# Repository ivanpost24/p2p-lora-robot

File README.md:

# WIoT final project

Authored by: Farjan Ahmed, Carlos Giron, Ivan Post

This is our final project for CS 4501: Wireless for the Internet of Things. It is a prototype system for controlling a mobile robot over long distances (from our observation, up to 0.32 km) using the LoRa physical layer protocol on Heltec ESP32 v3 LORA boards. It is designed to operate on the 915 MHz unlicensed band in the United States, which means you do not need an amateur radio license to use it. [This is a video of an operator controlling the robot from about 0.3 km away](https://drive.google.com/file/d/1XLk9izT9hsWHlGPpsFzeZ8Zzyy3jfpdS/view?usp=sharing); the control latency is primarily due to delays in the video feed and is under 500 ms in practice. The exact feasible range will depend on environmental factors.

We have provided instructions below to reproduce our prototype.

## Building the peripheral robot

### Components list:
* [WiFi LoRa 32 V3](https://heltec.org/project/wifi-lora-32-v3/) Heltec Board
* 2 [Sparkfun Dual tb6612fng Motor Drivers](https://www.sparkfun.com/sparkfun-motor-driver-dual-tb6612fng-1a.html) for motor control
* 4 [12V DC 100RPM Greartisan](amazon.com/Greartisan-Electric-Reduction-Centric-Diameter/dp/B072R57C56/ref=sr_1_6?crid=129Y1UB2Q6AGI&dib=eyJ2IjoiMSJ9.DwmBOBIYZeCSiQA5saHHIxj7DpqChe3S76xeKR8zBhYkiYd1JqMtlKpyXpX8ml9P-PodyTQpF1U53Aiup88Gdk4xNOoXEbOCuZ-eF9qleWwFV8hyrN2Rm18CDetzJ0f9fudnr4t8DZx4H_xdhjciGS_N9iVl0n4egDoUJzDH8lzn89O2e6Xu7hb-V0s1TQMCYfGA-40lgYDVYd1WclO5MOMkNcvgmsqaYL5KdbTtvnZBJRt6uXWlYDs0ATjglZvQkKjh9Chfi3PU3360LFzHv60yV7CS9oWNygZAhhukyWI.Be_9xpxrY9lM7WvLv97bnTWI3TeSQBAD8dNGXVNmA04&dib_tag=se&keywords=greartisan&qid=1778122489&sprefix=greara%2Caps%2C104&sr=8-6) Motors
* [INIU Portable Power Bank](https://www.amazon.com/INIU-Portable-Slimmest-Powerbank-Compatible/dp/B0DC9PV394/ref=sr_1_4?crid=18OPPD3YMVHBW&dib=eyJ2IjoiMSJ9.0WQzVjTrLphPpYXHXLB68u4mBA5Rbn288wfA5sWyp35DpGtrewRhO8osgHukWIII1DwwZKSDCB8bNecpqMsOLGRi4OvMCrledarzWXZo2mm3vVUFbNUYvgteSJSiUC4W4GYlY3ICUgLDd70C-CZUId6LxWdVb2gp8cnrTH14hRnbeg_DZL2gJpJ-KxWzOnmqB7snAoO4SP9RmN1tobYXKDJH2LOSkcSvpj6yAEEGyvA.t-OCLLBvhl4AjC0RjoiDnJkgwEFwfezcISsImUpkACE&dib_tag=se&keywords=inui%2Bpower%2Bbank&qid=1778122614&sprefix=inui%2Bpower%2Bbank%2B%2Caps%2C218&sr=8-4&th=1)
* [ACEIRMC USB Power Delivery Module](https://www.amazon.com/ACEIRMC-Trigger-Polling-Detector-Notebook/dp/B0BTHXKM91/ref=sxin_17_pa_sp_search_thematic_sspa?content-id=amzn1.sym.354b3233-22c2-4681-93ae-c50603e79747%3Aamzn1.sym.354b3233-22c2-4681-93ae-c50603e79747&crid=441D3EZMIEG8&cv_ct_cx=pd+module&keywords=pd+module&pd_rd_i=B0BTHXKM91&pd_rd_r=e3bb3bd6-a17f-436b-9dd3-0978a650ec78&pd_rd_w=KqERS&pd_rd_wg=o0LLY&pf_rd_p=354b3233-22c2-4681-93ae-c50603e79747&pf_rd_r=KJ86FRZV0K8ABR1RP7X3&qid=1778122403&s=electronics&sbo=RZvfv%2F%2FHxDF%2BO5021pAnSA%3D%3D&sprefix=pd+modul%2Celectronics%2C102&sr=1-1-9630ce6b-eb04-480e-8729-567d2ef7dacb-spons&aref=fOHUb9EmTP&sp_csd=d2lkZ2V0TmFtZT1zcF9zZWFyY2hfdGhlbWF0aWM&psc=1) for requesting 12V from a power bank
* [HiLetgo game joystick](amazon.com/HiLetgo-Controller-JoyStick-Breakout-Arduino/dp/B00P7QBGD2)

Additional pcb relevant components such as resistors, switches, and connectors are shown in this schematic:

The KiCad files for editing the schematic and gerbers for ordering PCBs are included in the "/KiCad" directory.

Mount the breakout boards for motor drivers and modules onto their respective locations on the pcb:

## Building the central controller
### Pin assignments:
Assignments for the peripheral robot device are as follows:
* 19 - PWMA/B
* 20 - A/BIN1
* 26 - A/BIN2
* 47 - PWMA/B
* 48 - A/BIN1
* 33 - A/BIN2
* Connect external 3v3 supply and gnd

These pins are used to set the direction of motors and speed of motors as they are connected to tb6612fng motor drivers. You **MUST NOT** power the motor drivers using the 3v3 pins of the Heltec board. Due to a hardware issue it seems that these boards are unable to power the motor drivers and remain on for operation. You must use a seperate 3v3 source to power the drivers.

In our case we used an *Arduino Uno R3* to deliver 3v3, but a simple battery should suffice. It is important to remember to ground both Arduino and Heltec on the same rail otherwise reference issues for digital logic occur.

Assignments for the central controller are as follows:
* 7 - Vrx
* 6 - Vry
* 5 - Sw

Although the datasheet recommends using 5V as input, our code was designed around using 3v3.

## Deploying the provided code

This project uses PlatformIO, so configuring the project locally should be simple. Flash the Heltec v3 on the robot with the lora-peripheral code, and flash the Heltec v3 on the controller with the lora-central code. Everything should start automatically without any user input.

## Starting the robot
After code has been flashed onto the central and peripheral devices start the device as follows:
1. Connect the power delivery module to the power bank's 65 W output port
2. Connect the Arduino to the power bank
3. Connect the Heltec to the power bank
4. Flip the enable switch

If the PD module and onboard led are on then the robot is ready for operation if the devices were flashed successfully and connections were correct.

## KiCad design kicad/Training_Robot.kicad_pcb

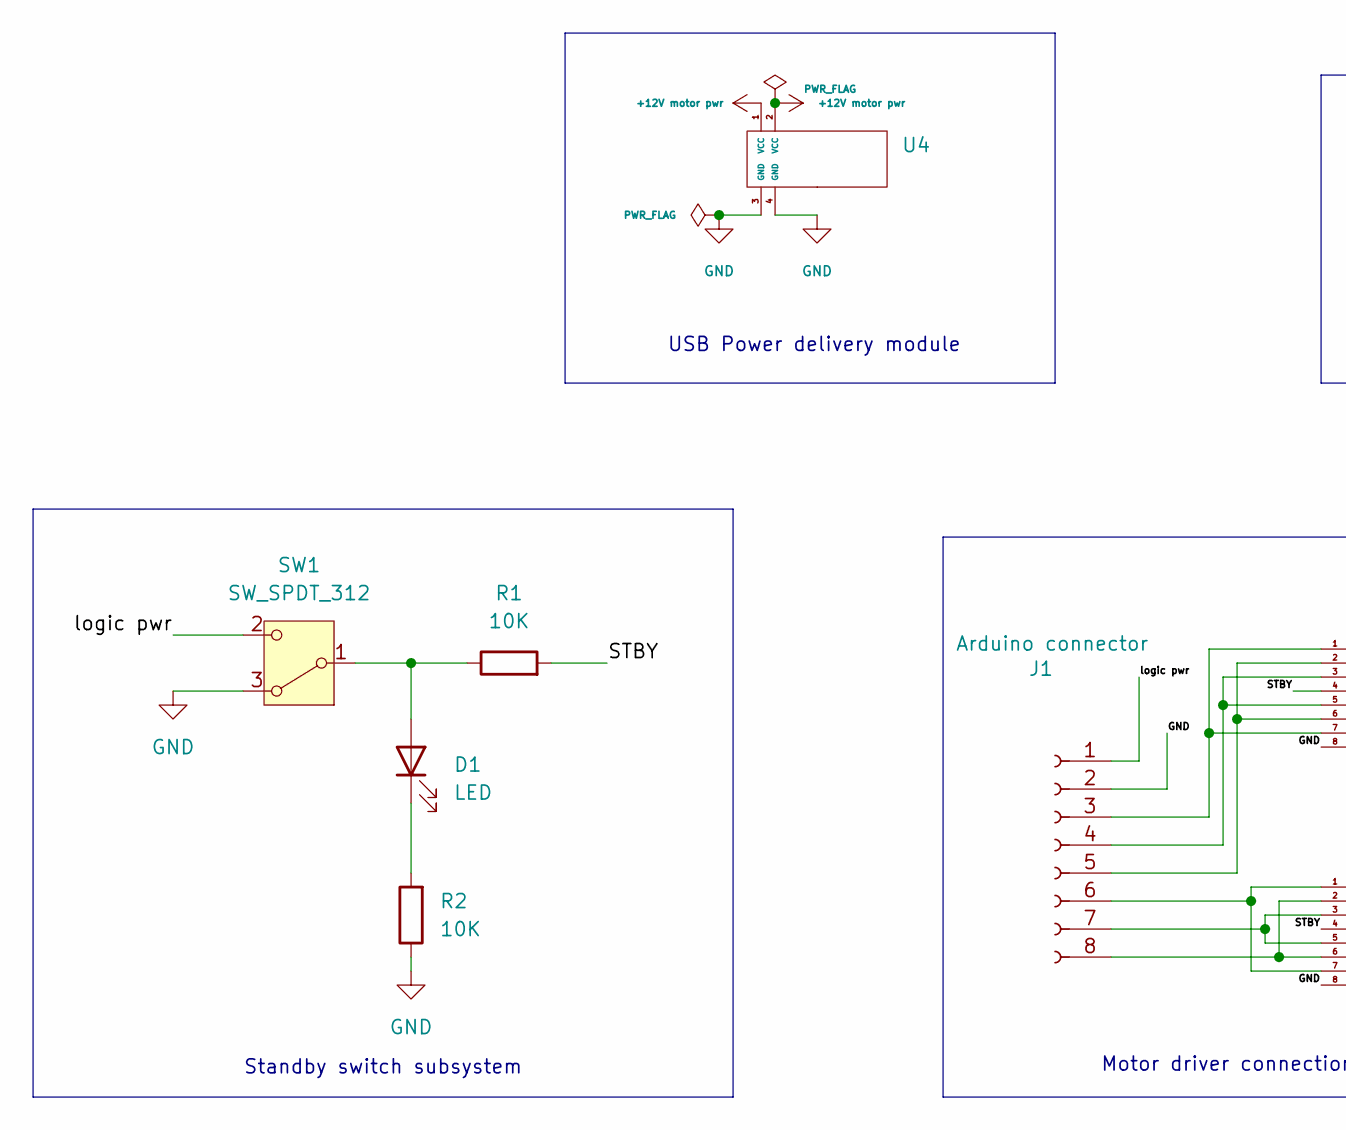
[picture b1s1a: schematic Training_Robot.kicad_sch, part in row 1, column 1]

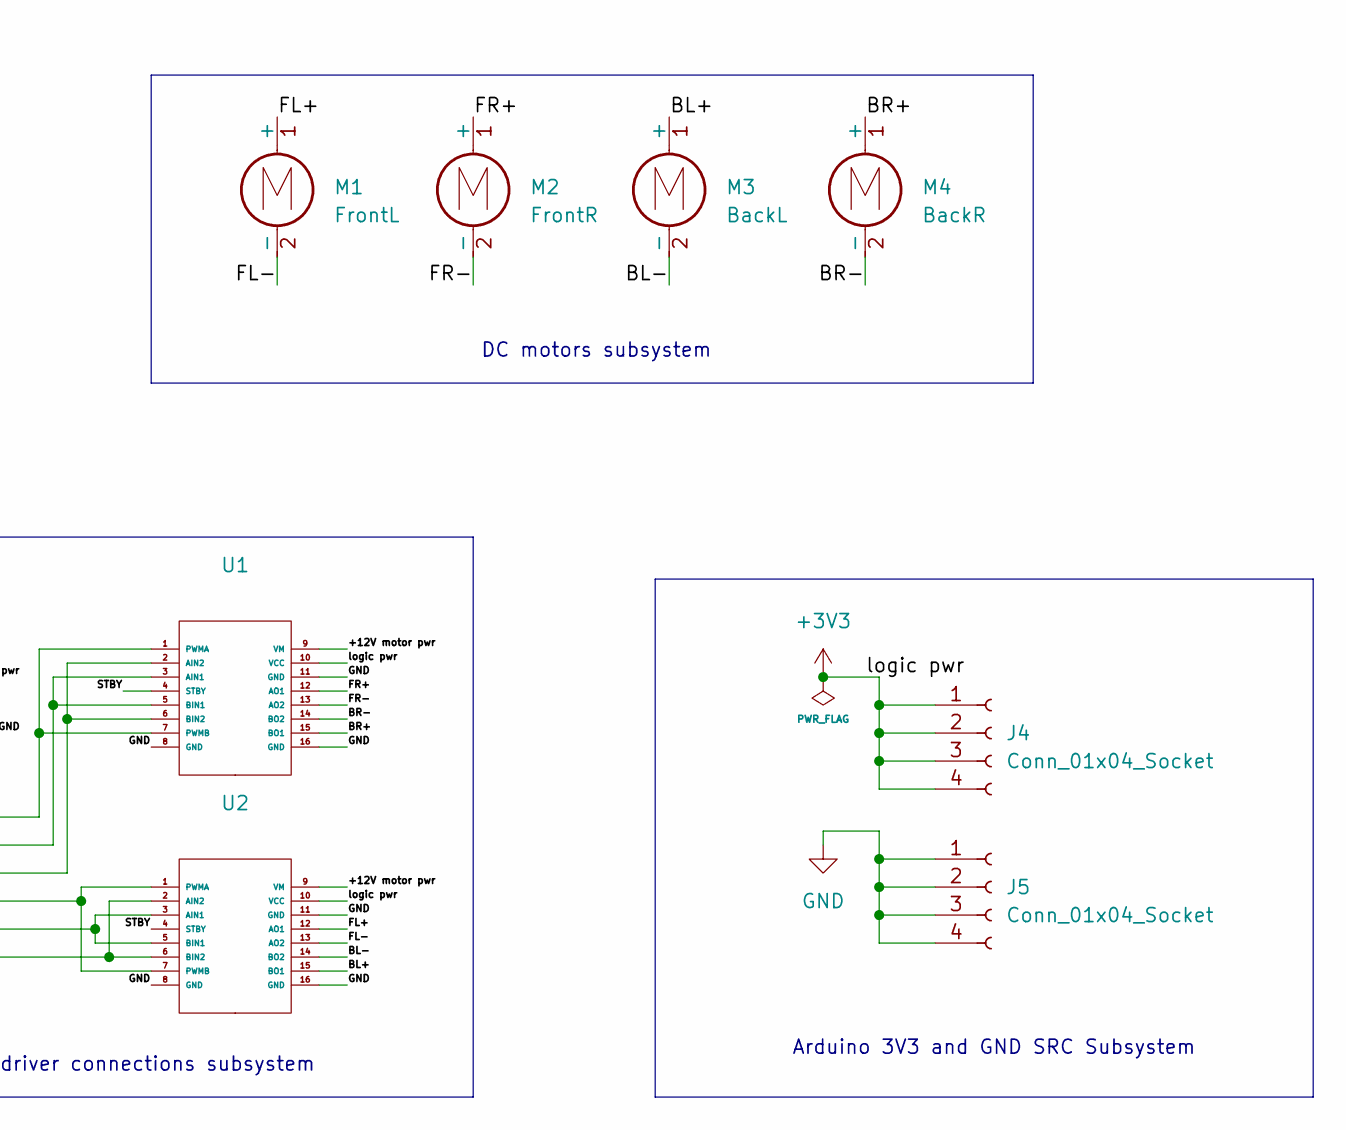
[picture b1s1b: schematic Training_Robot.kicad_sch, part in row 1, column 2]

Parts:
D1: LED; LED_D3.0mm
J1: Arduino connector; PinSocket_1x08_P2.54mm_Vertical
J4, J5: Conn_01x04_Socket; PinSocket_1x04_P2.54mm_Vertical
M1: FrontL; TerminalBlock_Phoenix_MKDS-1,5-2_1x02_P5.00mm_Horizontal
M2: FrontR; TerminalBlock_Phoenix_MKDS-1,5-2_1x02_P5.00mm_Horizontal
M3: BackL; TerminalBlock_Phoenix_MKDS-1,5-2_1x02_P5.00mm_Horizontal
M4: BackR; TerminalBlock_Phoenix_MKDS-1,5-2_1x02_P5.00mm_Horizontal
R1, R2: 10K; R_Axial_DIN0204_L3.6mm_D1.6mm_P5.08mm_Horizontal
SW1: SW_SPDT_312; SW_Slide_SPDT_Straight_CK_OS102011MS2Q
U1, U2: TB_breakout_motor_driver
U4: PD Module

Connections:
+3V3: J1.1, J4.1, J4.2, J4.3, J4.4, SW1.2 (C), U1.10 (VCC), U2.10 (VCC)
+12V motor pwr: U1.9 (VM), U2.9 (VM), U4.1 (VCC), U4.2 (VCC)
/BL+: M3.1 (+), U2.15 (BO1)
/BL-: M3.2 (-), U2.14 (BO2)
/BR+: M4.1 (+), U1.15 (BO1)
/BR-: M4.2 (-), U1.14 (BO2)
/FL+: M1.1 (+), U2.12 (AO1)
/FL-: M1.2 (-), U2.13 (AO2)
/FR+: M2.1 (+), U1.12 (AO1)
/FR-: M2.2 (-), U1.13 (AO2)
/STBY: R1.2, U1.4 (STBY), U2.4 (STBY)
GND: J1.2, J5.1, J5.2, J5.3, J5.4, R2.1, SW1.3 (A), U1.8 (GND), U1.11 (GND), U1.16 (GND), U2.8 (GND), U2.11 (GND), U2.16 (GND), U4.3 (GND), U4.4 (GND)
unnamed: D1.2 (A), R1.1, SW1.1 (B)
unnamed: D1.1 (K), R2.2
unnamed: J1.3, U1.1 (PWMA), U1.7 (PWMB)
unnamed: J1.4, U1.3 (AIN1), U1.5 (BIN1)
unnamed: J1.5, U1.2 (AIN2), U1.6 (BIN2)
unnamed: J1.6, U2.1 (PWMA), U2.7 (PWMB)
unnamed: J1.7, U2.3 (AIN1), U2.5 (BIN1)
unnamed: J1.8, U2.2 (AIN2), U2.6 (BIN2)

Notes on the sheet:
DC motors subsystem
Standby switch subsystem
USB Power delivery module
Arduino 3V3 and GND SRC Subsystem
Motor driver connections subsystem

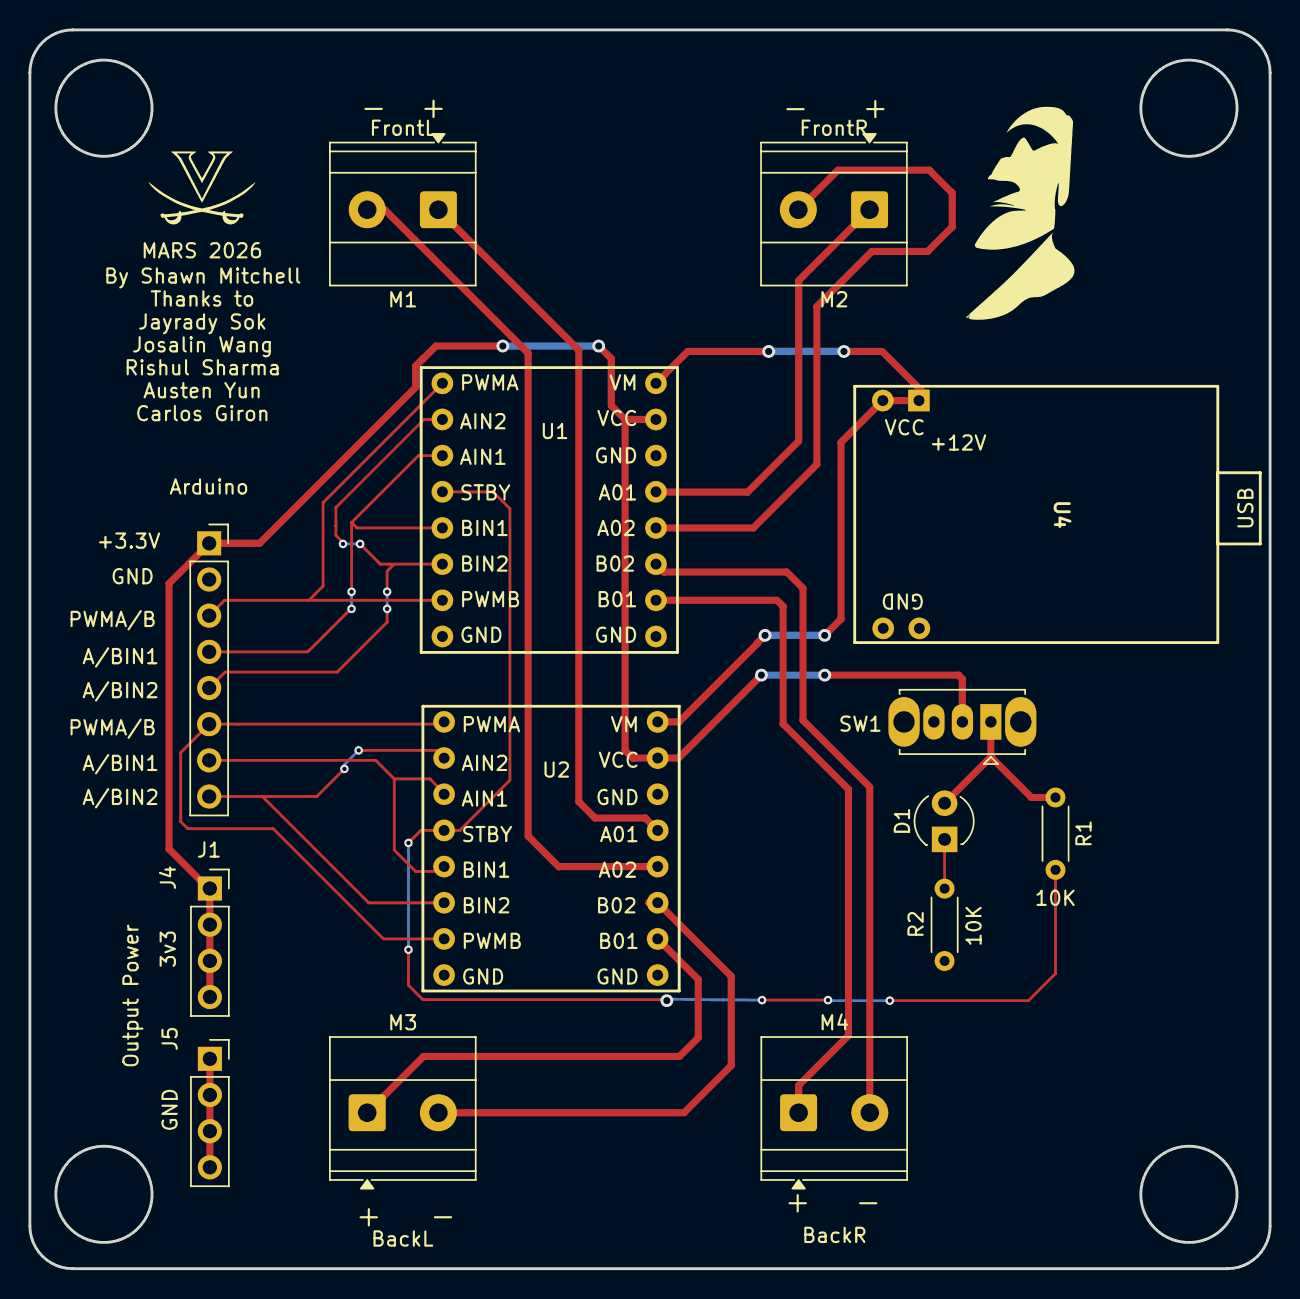
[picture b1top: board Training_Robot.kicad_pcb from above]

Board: 2 copper layers, 87.1 x 87.0 mm, 14 parts (0 on the bottom side), 20 nets.

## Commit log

2026-04-14 Add root-level .gitignore
2026-04-27 Added data structures for the connection protocol
2026-04-27 Add public accessor for data
2026-04-28 Fix a few issues
2026-04-28 Fix const-correctness
2026-04-28 Add copy and conversion constructors for the rest of the packet types
2026-04-28 Added packet type assertions in conversion constructors (to prevent accidental conversions)
2026-04-30 Expand window size and add more utility methods
2026-04-30 First attempt at peripheral implementation (untested)
2026-04-30 First attempt at central device counter (untested)
2026-05-01 First working example of connections, but they're super unreliable
2026-05-01 Changed protocol to achieve TDMA with alternating RX windows instead of time slots
2026-05-01 added dir for robot control code
2026-05-01 Provide a nice function interface for TX/RX
2026-05-01 Add a setup function for convenience
2026-05-01 Add missing performSetup() declaration and usage in main for lora-central
2026-05-01 added joystick code changes
2026-05-01 fixed bounds and mem usage for joystick
2026-05-01 Demo day version, fully functional
2026-05-04 Increase SF to 9
2026-05-05 Change packet format to accommodate frequency hopping
2026-05-05 Updated central device to use FHSS
2026-05-06 Massive refactor and implemented FHSS
2026-05-06 Tried increasing bandwidth to 250 kHz...it's even less reliable than before
2026-05-06 Increased spreading factor to 10 and TX power to 22 dB
2026-05-07 Removed redundant packet length from connection data message
2026-05-07 Added more tolerance for missed packets
2026-05-07 Added motor command message for better debugging
2026-05-07 Add to lora-central README
2026-05-07 Added to lora-peripheral README
2026-05-07 added test code for ultrasonic and BNO055 imu and fixed printing for robot_control
2026-05-07 Added to README.md and deleted unnecessary directories
2026-05-07 added images and gerbers for pcb
2026-05-07 added
2026-05-07 Added description on pushing code
